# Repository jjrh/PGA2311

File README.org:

* PGA2311 KICAD board.
  http://www.ti.com/lit/ds/sbos218a/sbos218a.pdf

* images
    #+CAPTION: schematic
    #+NAME:   fig:0
    #+attr_html: :width 800px
    [[./images/pga2311.png]]

    #+CAPTION: 3d1
    #+NAME:   fig:1
    #+attr_html: :width 800px
    [[./images/3d1.png]]

    #+CAPTION: 3d2
    #+NAME:   fig:2
    #+attr_html: :width 800px
    [[./images/3d2.png]]

    #+CAPTION: pcb back
    #+NAME:   fig:3
    #+attr_html: :width 800px
    [[./images/back.png]]

    #+CAPTION: pcb front
    #+NAME:   fig:4
    #+attr_html: :width 800px
    [[./images/front.png]]

    #+CAPTION: pcb-B_Cu
    #+NAME:   fig:2
    #+attr_html: :width 800px
    [[./images/pga2311-B_Cu.png]]

    #+CAPTION: pcb-F_Cu
    #+NAME:   fig:2
    #+attr_html: :width 800px
    [[./images/pga2311-F_Cu.png]]

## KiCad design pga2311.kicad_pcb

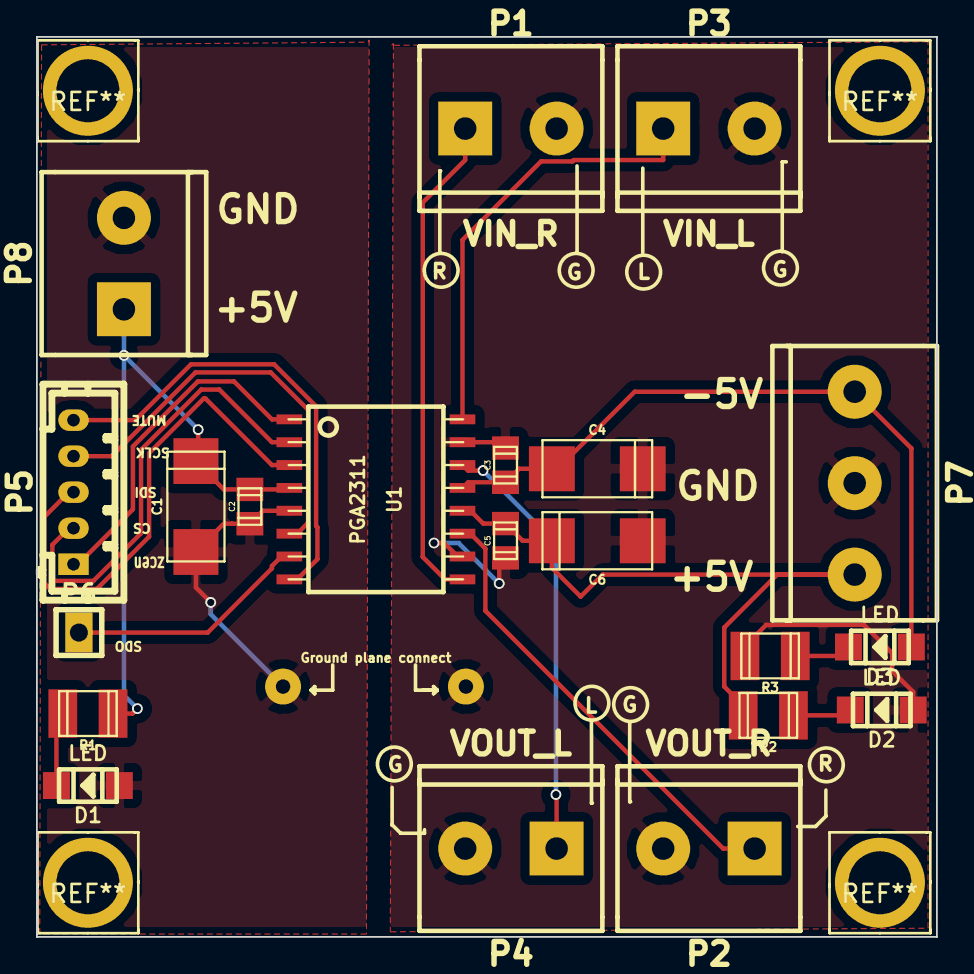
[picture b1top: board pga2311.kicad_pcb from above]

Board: 2 copper layers, 50.0 x 50.0 mm, 21 parts (0 on the bottom side), 18 nets.

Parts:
C1, C4, C6: 10uF; c_tant_C
C2, C3, C5: 0.1uF; c_0805
D1, D2, D3: LED; Led_1206
P1: VIN_R; mors_2p
P2: VOUT_R; mors_2p
P3: VIN_L; mors_2p
P4: VOUT_L; mors_2p
P5: b5b-ph-kl
P6: SDO_TO_OTHER_PGA2311; pin_strip_1
P7: mors_3p_inv_pins
P8: mors_2p
R1, R2, R3: 10k; r_1210
U1: PGA2311; soic-16

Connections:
+5V: C5.1, C6.1, P7.1, R2.1, U1.12
+5VD: C1.1, C2.1, P8.1, R1.2, U1.4
-5V: C3.2, C4.2, D3.1, P7.3, U1.13
CS: P5.2, U1.2
GND_A: C3.1, C4.1, C5.2, C6.2, D2.1, P1.2, P2.2, P3.2, P4.2, P7.2, R3.1, U1.10, U1.15
GND_D: C1.2, C2.2, D1.1, P8.2, U1.5
MUTE: P5.5, U1.8
unnamed: D1.2, R1.1
unnamed: D2.2, R2.2
unnamed: D3.2, R3.2
SCLK: P5.4, U1.6
SDI: P5.3, U1.3
SDO: P6.1, U1.7
VIN_L: P3.1, U1.16
VIN_R: P1.1, U1.9
VOUT_L: P4.1, U1.14
VOUT_R: P2.1, U1.11
ZCEN: P5.1, U1.1

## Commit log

2015-08-29 initialized repo
2015-08-29 added images and readme
2016-04-17 before making changes
